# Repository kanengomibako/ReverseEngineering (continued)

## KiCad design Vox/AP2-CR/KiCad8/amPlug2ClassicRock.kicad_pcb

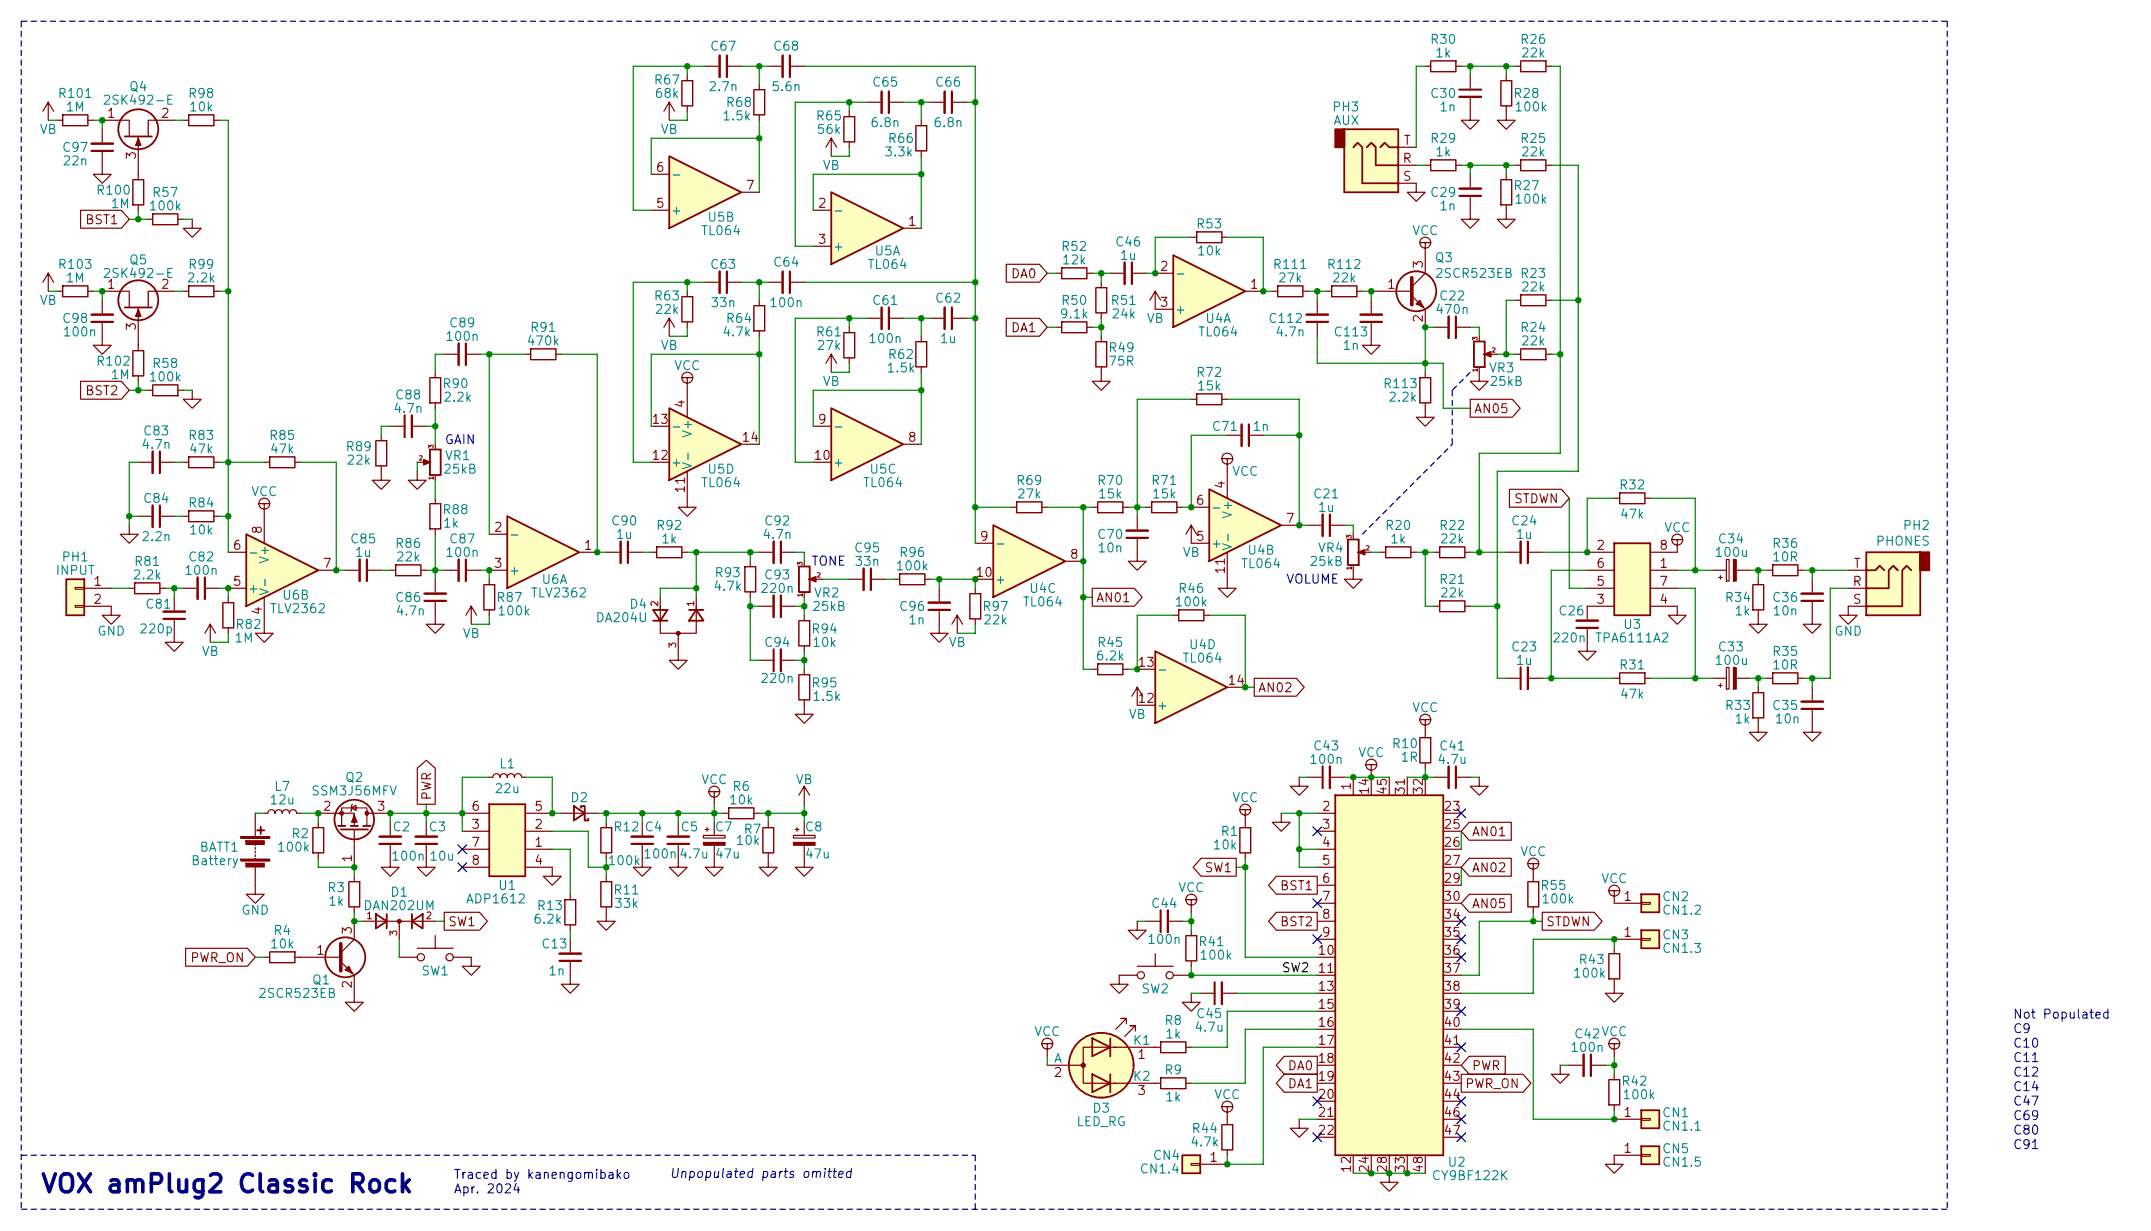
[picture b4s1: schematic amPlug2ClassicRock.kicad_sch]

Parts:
BATT1: Battery; my_conn
C2, C4, C42, C43, C44, C61, C64, C82, C87, C89, C98: 100n; C_0603_1608Metric
C3: 10u; C_0805_2012Metric
C5, C41, C45: 4.7u; C_0603_1608Metric
C7, C8: 47u; CP_Elec_5x5.4
C13, C29, C30, C71, C96, C113: 1n; C_0603_1608Metric
C21, C23, C24, C46, C62, C85, C90: 1u; C_0603_1608Metric
C22: 470n; C_0603_1608Metric
C26, C93, C94: 220n; C_0603_1608Metric
C33, C34: 100u; CP_Elec_5x5.4
C35, C36, C70: 10n; C_0603_1608Metric
C63, C95: 33n; C_0603_1608Metric
C65, C66: 6.8n; C_0603_1608Metric
C67: 2.7n; C_0603_1608Metric
C68: 5.6n; C_0603_1608Metric
C81: 220p; C_0603_1608Metric
C83, C86, C88, C92, C112: 4.7n; C_0603_1608Metric
C84: 2.2n; C_0603_1608Metric
C97: 22n; C_0603_1608Metric
CN1: CN1.1; my_SmallestPad_0-72mmDrill
CN2: CN1.2; my_SmallestPad_0-72mmDrill
CN3: CN1.3; my_SmallestPad_0-72mmDrill
CN4: CN1.4; my_SmallestPad_0-72mmDrill
CN5: CN1.5; my_SmallestPad_0-72mmDrill
D1: DAN202UM; SOT-323_SC-70
D2: ?; D_SOD-323
D3: LED_RG; PinHeader_1x03_P2.54mm_Vertical
D4: DA204U; SOT-323_SC-70
L1: 22u; L_2512_6332Metric
L7: 12u; R_0603_1608Metric
PH1: INPUT; my_conn
PH2: PHONES; Jack_3.5mm_CUI_SJ-3523-SMT_Horizontal
PH3: AUX; Jack_3.5mm_CUI_SJ-3523-SMT_Horizontal
Q1, Q3: 2SCR523EB; SOT-523
Q2: SSM3J56MFV; SOT-723
Q4, Q5: 2SK492-E; SOT-23
R1, R4, R6, R7, R53, R84, R94, R98: 10k; R_0603_1608Metric
R2, R12, R27, R28, R41, R42, R43, R46, R55, R57, R58, R87, R96: 100k; R_0603_1608Metric
R3, R8, R9, R20, R29, R30, R33, R34, R88, R92: 1k; R_0603_1608Metric
R10: 1R; R_0603_1608Metric
R11: 33k; R_0603_1608Metric
R13, R45: 6.2k; R_0603_1608Metric
R21, R22, R23, R24, R25, R26, R63, R86, R89, R97, R112: 22k; R_0603_1608Metric
R31, R32, R83, R85: 47k; R_0603_1608Metric
R35, R36: 10R; R_1206_3216Metric
R44, R64, R93: 4.7k; R_0603_1608Metric
R49: 75R; R_0603_1608Metric
R50: 9.1k; R_0603_1608Metric
R51: 24k; R_0603_1608Metric
R52: 12k; R_0603_1608Metric
R61, R69, R111: 27k; R_0603_1608Metric
R62, R68, R95: 1.5k; R_0603_1608Metric
R65: 56k; R_0603_1608Metric
R66: 3.3k; R_0603_1608Metric
R67: 68k; R_0603_1608Metric
R70, R71, R72: 15k; R_0603_1608Metric
R81, R90, R99, R113: 2.2k; R_0603_1608Metric
R82, R100, R101, R102, R103: 1M; R_0603_1608Metric
R91: 470k; R_0603_1608Metric
SW1: SW1; my_conn
SW2: SW2; my_conn
U1: ADP1612; MSOP-8_3x3mm_P0.65mm
U2: CY9BF122K; QFN-48-1EP_7x7mm_P0.5mm_EP5.1x5.1mm
U3: TPA6111A2; SOIC-8_3.9x4.9mm_P1.27mm
U4, U5: TL064; TSSOP-14_4.4x5mm_P0.65mm
U6: TLV2362; TSSOP-8_4.4x3mm_P0.65mm
VR1, VR2, VR3, VR4: 25kB; my_Pot_disk_smd

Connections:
/SW2: R41.2, SW2.1, U2.11
AN01: R45.1, R69.2, R70.2, U2.25, U2.26, U4.8
AN02: R46.2, U2.27, U2.29, U4.14
AN05: C22.2, C112.1, Q3.2 (E), R113.1, U2.30
BST1: R57.1, R100.1, U2.6
BST2: R58.2, R102.1, U2.8
DA0: R52.1, U2.18
DA1: R50.1, U2.19
GND: BATT1.2 (-), C2.1, C3.1, C4.1, C5.1, C7.2, C8.2, C13.1, C26.1, C29.1, C30.2, C35.1, C36.1, C41.1, C42.2, C43.1, C44.1, C45.1, C70.1, C81.1, C83.2, C84.2, C86.1, C96.1, C97.1, C98.1, C113.1, CN5.1, D4.3, PH1.2, PH2.S, PH3.S, Q1.2 (E), R7.2, R11.2, R27.1, R28.2, R33.1, R34.1, R43.1, R49.2, R57.2, R58.1, R89.2, R95.2, R113.2, SW1.2, SW2.2, U1.4, U2.2, U2.4, U2.5, U2.12, U2.21, U2.24, U2.28, U2.33, U2.48, U3.4, U4.11 (V-), U5.11 (V-), U6.4 (V-), VR1.2, VR3.1, VR4.1
unnamed: BATT1.1 (+), L7.1
unnamed: C13.2, R13.2
unnamed: C21.1, VR4.3
unnamed: C21.2, C71.1, R72.2, U4.7
unnamed: C22.1, VR3.3
unnamed: C23.1, R21.2, R23.2, R25.2
unnamed: C24.2, R22.2, R24.1, R26.1
unnamed: C29.2, R25.1, R27.2, R29.2
unnamed: C30.1, R26.2, R28.1, R30.1
unnamed: C33.2, R33.2, R35.1
unnamed: C34.2, R34.2, R36.1
unnamed: C35.2, PH2.R, R35.2
unnamed: C36.2, PH2.T, R36.2
unnamed: C46.2, R51.1, R52.2
unnamed: C61.1, C62.2, R62.1
unnamed: C63.1, C64.2, R64.2
unnamed: C65.1, C66.2, R66.1
unnamed: C67.1, C68.2, R68.1
unnamed: C70.2, R70.1, R71.1, R72.1
unnamed: C81.2, C82.2, R81.2
unnamed: C83.1, R83.1
unnamed: C84.1, R84.1
unnamed: C85.1, R86.1
unnamed: C85.2, R85.2, U6.7
unnamed: C86.2, C87.2, R86.2, R88.1
unnamed: C88.1, R89.1
unnamed: C88.2, R90.1, VR1.3
unnamed: C89.2, R90.2
unnamed: C90.1, R92.1
unnamed: C90.2, R91.2, U6.1
unnamed: C92.1, VR2.3
unnamed: C92.2, D4.1, D4.2, R92.2, R93.1
unnamed: C93.1, R94.1, VR2.1
unnamed: C93.2, C94.1, R93.2
unnamed: C94.2, R94.2, R95.1
unnamed: C95.1, R96.1
unnamed: C95.2, VR2.2
unnamed: C112.2, R111.2, R112.1
unnamed: CN1.1, R42.1, U2.40
unnamed: CN3.1, R43.2, U2.38
unnamed: CN4.1, R44.2, U2.17
unnamed: D1.3, SW1.1
unnamed: D2.2 (A), L1.2, U1.5
unnamed: D3.1 (K1), R8.1
unnamed: D3.3 (K2), R9.1
unnamed: PH1.1, R81.1
unnamed: PH3.R, R29.1
unnamed: PH3.T, R30.2
unnamed: Q1.1 (B), R4.1
unnamed: D1.1, Q1.3 (C), R3.2
unnamed: Q2.1 (G), R2.1, R3.1
unnamed: L7.2, Q2.2 (S), R2.2
unnamed: C113.2, Q3.1 (B), R112.2
unnamed: Q4.2 (D), R98.1
unnamed: Q4.3 (G), R100.2
unnamed: C97.2, Q4.1 (S), R101.2
unnamed: Q5.2 (D), R99.1
unnamed: Q5.3 (G), R102.2
unnamed: C98.2, Q5.1 (S), R103.2
unnamed: R20.1, VR4.2
unnamed: R20.2, R21.1, R22.1
unnamed: R23.1, R24.2, VR3.2
unnamed: R49.1, R50.2, R51.2
unnamed: R88.2, VR1.1
unnamed: R53.2, R111.1, U4.1
unnamed: R13.1, U1.1
unnamed: R11.1, R12.2, U1.2
unnamed: C45.2, U2.13
unnamed: R8.2, U2.15
unnamed: R9.2, U2.16
unnamed: C41.2, R10.2, U2.31, U2.32
unnamed: C34.1, R32.2, U3.1
unnamed: C24.1, R32.1, U3.2
unnamed: C26.2, U3.3
unnamed: C23.2, R31.2, U3.6
unnamed: C33.1, R31.1, U3.7
unnamed: C46.1, R53.1, U4.2 (-)
unnamed: C71.2, R71.2, U4.6 (-)
unnamed: C96.2, R96.2, R97.1, U4.10 (+)
unnamed: C62.1, C64.1, C66.1, C68.1, R69.1, U4.9 (-)
unnamed: R45.2, R46.1, U4.13 (-)
unnamed: C65.2, R65.1, U5.3 (+)
unnamed: R66.2, U5.1, U5.2 (-)
unnamed: C67.2, R67.1, U5.5 (+)
unnamed: R68.2, U5.6 (-), U5.7
unnamed: C61.2, R61.1, U5.10 (+)
unnamed: R62.2, U5.8, U5.9 (-)
unnamed: C63.2, R63.1, U5.12 (+)
unnamed: R64.1, U5.13 (-), U5.14
unnamed: C87.1, R87.1, U6.3 (+)
unnamed: C89.1, R91.1, U6.2 (-)
unnamed: C82.1, R82.1, U6.5 (+)
unnamed: R83.2, R84.2, R85.1, R98.2, R99.2, U6.6 (-)
PWR: C2.2, C3.2, L1.1, Q2.3 (D), U1.3, U1.6, U2.42
PWR_ON: R4.2, U2.43
STDWN: R55.2, U2.37, U3.5
SW1: D1.2, R1.2, U2.10
VB: C8.1, R6.2, R7.1, R61.2, R63.2, R65.2, R67.2, R82.2, R87.2, R97.2, R101.1, R103.1, U4.3 (+), U4.5 (+), U4.12 (+)
VCC: C4.2, C5.2, C7.1, C42.1, C43.2, C44.2, CN2.1, D2.1 (K), D3.2 (A), Q3.3 (C), R1.1, R6.1, R10.1, R12.1, R41.1, R42.2, R44.1, R55.1, U2.1, U2.14, U2.45, U3.8, U4.4 (V+), U5.4 (V+), U6.8 (V+)

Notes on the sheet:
VOX amPlug2 Classic Rock
GAIN
TONE
Unpopulated parts omitted
Not Populated C9 C10 C11 C12 C14 C47 C69 C80 C91
Traced by kanengomibako Apr. 2024
VOLUME

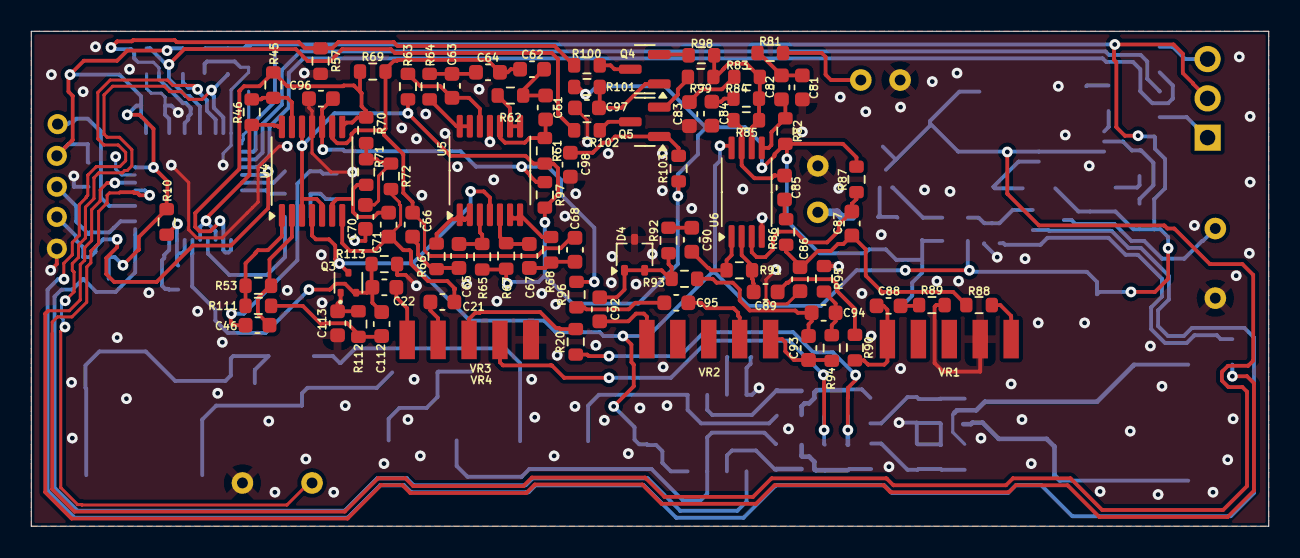
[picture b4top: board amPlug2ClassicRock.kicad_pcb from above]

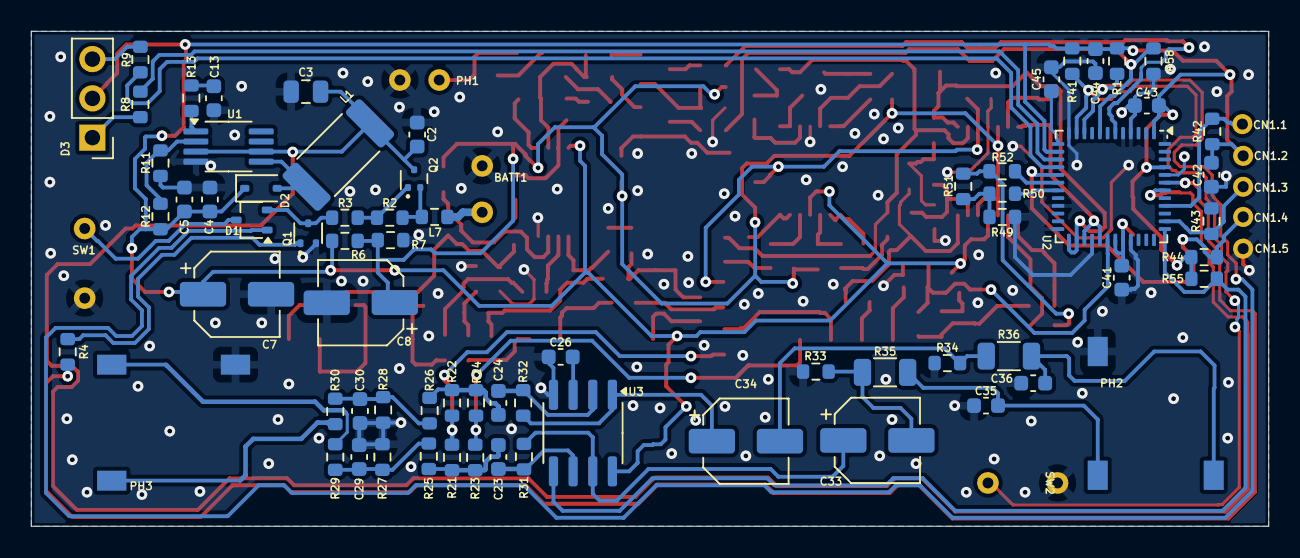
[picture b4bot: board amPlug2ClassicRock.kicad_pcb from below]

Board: 2 copper layers, 80.0 x 32.0 mm, 166 parts (79 on the bottom side), 108 nets.
